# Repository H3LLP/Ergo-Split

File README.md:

# Ergo-Split
Ergonomic Split keyboard
A somewhat low-profile wireless 46-key keyboard that uses a dongle for connection.
Supports Choc V1 and V2 switches, is hotswappable, and uses a 3.7V 800mAh 802535 for each side. PCB is screwed into the case with 2 M2x6 screws and self-taps.

Dongle Case: https://www.printables.com/model/651428-seeed-xiao-ble-case-with-led-hole
(Not made by me)

Firmware is ZMK

AI Disclosure:
Used AI to help with part selection and parts of the firmware

The schematic for the PCB is the same for both sides

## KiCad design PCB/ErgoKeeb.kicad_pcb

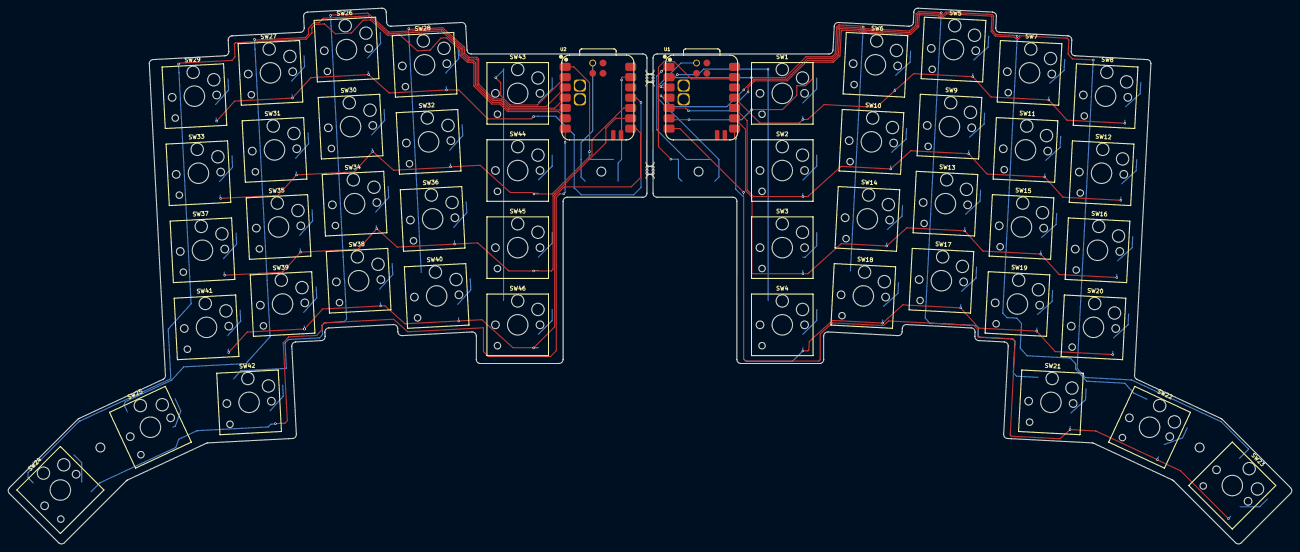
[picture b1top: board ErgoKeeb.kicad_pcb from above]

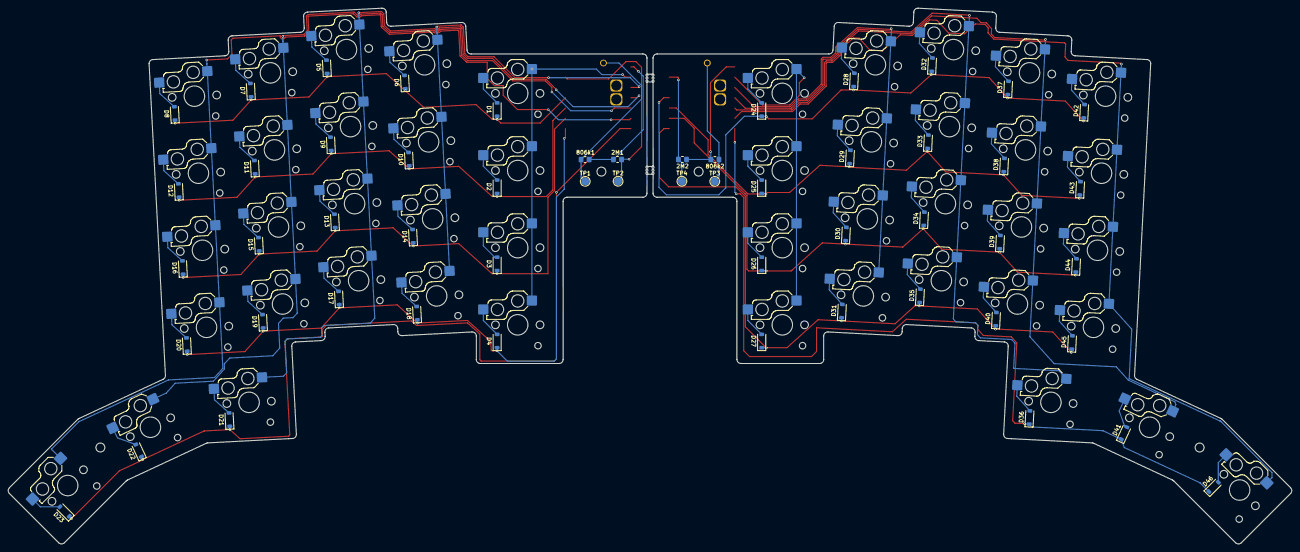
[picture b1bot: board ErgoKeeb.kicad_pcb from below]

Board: 2 copper layers, 316.9 x 132.3 mm, 108 parts (54 on the bottom side), 72 nets.

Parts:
2M1, 2M2: R3; R_0805_2012Metric_Pad1.20x1.40mm_HandSolder
806k1, 806k2: R1; R_0805_2012Metric_Pad1.20x1.40mm_HandSolder
BO1, BO2: MountingHole; mouse-bite-2mm-slot
D1, D2, D3, D4, D5, D6, D7, D8, D9, D10, D11, D12, D13, D14, D15, D16, D17, D18, D19, D20, D21, D22, D23, D24, D25, D26, D27, D28, D29, D30, D31, D32, D33, D34, D35, D36, D37, D38, D39, D40, D41, D42, D43, D44, D45, D46: D; D_SOD-123
H1, H2, H3, H4: MountingHole; MountingHole_2.2mm_M2
SW1, SW2, SW3, SW4, SW5, SW6, SW7, SW8, SW9, SW10, SW11, SW12, SW13, SW14, SW15, SW16, SW17, SW18, SW19, SW20, SW21, SW22, SW23, SW24, SW25, SW26, SW27, SW28, SW29, SW30, SW31, SW32, SW33, SW34, SW35, SW36, SW37, SW38, SW39, SW40, SW41, SW42, SW43, SW44, SW45, SW46: SW_Hotswap_Kailh_Choc_V1V2_1.00u
TP1, TP3: BAT; TestPoint_Pad_D2.0mm
TP2, TP4: GND; TestPoint_Pad_D2.0mm
U1, U2: XIAO-nRF52840-SMD; modified-XIAO-nRF52840-SMD

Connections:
/left/BT_PIN: 2M1.1, 806k1.2, U1.1 (D0)
/left/Ground: 2M1.2, TP2.1 (1_1), U1.13 (GND)
/left/VBAT: 806k1.1, TP1.1 (1_1), U1.19 (VBAT)
/left/col 0: SW1.1, SW2.1, SW3.1, SW4.1, U1.2 (D1)
/left/col 1: SW6.1, SW10.1, SW14.1, SW18.1, U1.3 (D2)
/left/col 2: SW5.1, SW9.1, SW13.1, SW17.1, SW21.1, U1.4 (D3)
/left/col 3: SW7.1, SW11.1, SW15.1, SW19.1, SW22.1, U1.5 (D4)
/left/col 4: SW8.1, SW12.1, SW16.1, SW20.1, SW23.1, U1.6 (D5)
/left/row 0: D1.1 (K), D5.1 (K), D6.1 (K), D7.1 (K), D8.1 (K), U1.11 (D10)
/left/row 1: D2.1 (K), D9.1 (K), D10.1 (K), D11.1 (K), D12.1 (K), U1.10 (D9)
/left/row 2: D3.1 (K), D13.1 (K), D14.1 (K), D15.1 (K), D16.1 (K), U1.9 (D8)
/left/row 3: D4.1 (K), D17.1 (K), D18.1 (K), D19.1 (K), D20.1 (K), U1.8 (D7)
/left/row 4: D21.1 (K), D22.1 (K), D23.1 (K), U1.7 (D6)
/right/BT_PIN: 2M2.1, 806k2.2, U2.1 (D0)
/right/Ground: 2M2.2, TP4.1 (1_1), U2.13 (GND)
/right/VBAT: 806k2.1, TP3.1 (1_1), U2.19 (VBAT)
/right/col 0: SW43.1, SW44.1, SW45.1, SW46.1, U2.2 (D1)
/right/col 1: SW28.1, SW32.1, SW36.1, SW40.1, U2.3 (D2)
/right/col 2: SW26.1, SW30.1, SW34.1, SW38.1, SW42.1, U2.4 (D3)
/right/col 3: SW25.1, SW27.1, SW31.1, SW35.1, SW39.1, U2.5 (D4)
/right/col 4: SW24.1, SW29.1, SW33.1, SW37.1, SW41.1, U2.6 (D5)
/right/row 0: D24.1 (K), D28.1 (K), D32.1 (K), D37.1 (K), D42.1 (K), U2.11 (D10)
/right/row 1: D25.1 (K), D29.1 (K), D33.1 (K), D38.1 (K), D43.1 (K), U2.10 (D9)
/right/row 2: D26.1 (K), D30.1 (K), D34.1 (K), D39.1 (K), D44.1 (K), U2.9 (D8)
/right/row 3: D27.1 (K), D31.1 (K), D35.1 (K), D40.1 (K), D45.1 (K), U2.8 (D7)
/right/row 4: D36.1 (K), D41.1 (K), D46.1 (K), U2.7 (D6)
unnamed: D1.2 (A), SW1.2
unnamed: D2.2 (A), SW2.2
unnamed: D3.2 (A), SW3.2
unnamed: D4.2 (A), SW4.2
unnamed: D5.2 (A), SW5.2
unnamed: D6.2 (A), SW6.2
unnamed: D7.2 (A), SW7.2
unnamed: D8.2 (A), SW8.2
unnamed: D9.2 (A), SW9.2
unnamed: D10.2 (A), SW10.2
unnamed: D11.2 (A), SW11.2
unnamed: D12.2 (A), SW12.2
unnamed: D13.2 (A), SW13.2
unnamed: D14.2 (A), SW14.2
unnamed: D15.2 (A), SW15.2
unnamed: D16.2 (A), SW16.2
unnamed: D17.2 (A), SW17.2
unnamed: D18.2 (A), SW18.2
unnamed: D19.2 (A), SW19.2
unnamed: D20.2 (A), SW20.2
unnamed: D21.2 (A), SW21.2
unnamed: D22.2 (A), SW22.2
unnamed: D23.2 (A), SW23.2
unnamed: D24.2 (A), SW43.2
unnamed: D25.2 (A), SW44.2
unnamed: D26.2 (A), SW45.2
unnamed: D27.2 (A), SW46.2
unnamed: D28.2 (A), SW28.2
unnamed: D29.2 (A), SW32.2
unnamed: D30.2 (A), SW36.2
unnamed: D31.2 (A), SW40.2
unnamed: D32.2 (A), SW26.2
unnamed: D33.2 (A), SW30.2
unnamed: D34.2 (A), SW34.2
unnamed: D35.2 (A), SW38.2
unnamed: D36.2 (A), SW42.2
unnamed: D37.2 (A), SW27.2
unnamed: D38.2 (A), SW31.2
unnamed: D39.2 (A), SW35.2
unnamed: D40.2 (A), SW39.2
unnamed: D41.2 (A), SW25.2
unnamed: D42.2 (A), SW29.2
unnamed: D43.2 (A), SW33.2
unnamed: D44.2 (A), SW37.2
unnamed: D45.2 (A), SW41.2
unnamed: D46.2 (A), SW24.2

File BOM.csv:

Part,Type,Quantity,Unit price (USD),Line total (USD),Link,Vendor,Funding,Notes,Designator,Footprint,Value
0805 SMD Resistor 2M Ohms,Part,2,2.81,2.81,https://www.aliexpress.us/item/3256806797741926.html,,Grant,,"2M1, 2M2",0805,R3
0805 SMD Resistor 806K Ohms,Part,2,2.27,2.27,https://www.aliexpress.us/item/3256804997915352.html,,Grant,,"806K1, 806K2",0805,R1
1N4148W T4 SOD-123,Part,46,3.60,3.60,https://www.aliexpress.us/item/3256811977042224.html,,Grant,,"D1, D10, D11, D12, D13, D14, D15, D16, D17, D18, D19, D2, D20, D21, D22, D23, D24, D25, D26, D27, D28, D29, D3, D30, D31, D32, D33, D34, D35, D36, D37, D38, D39, D4, D40, D41, D42, D43, D44, D45, D...",D_SOD-123,D
Kalih Choc Low Profile Socket,Part,46,7.37,7.37,https://www.aliexpress.us/item/3256808357010978.html,,Grant,,"SW1, SW10, SW11, SW12, SW13, SW14, SW15, SW16, SW17, SW18, SW19, SW2, SW20, SW21, SW22, SW23, SW24, SW25, SW26, SW27, SW28, SW29, SW3, SW30, SW31, SW32, SW33, SW34, SW35, SW36, SW37, SW38, SW39, SW...",SW_Hotswap_Kailh_Choc_V1V2_1.00u,~
XIAO nRF52840,Part,3,32.08,32.08,https://www.aliexpress.us/item/3256808047100037.html,,Grant,,"U1, U2",modified-XIAO-nRF52840-SMD,XIAO-nRF52840-SMD
Any Choc V1/V2 Switches,Part,46,28.23,28.23,https://www.aliexpress.us/item/3256808697103313.html,,Grant,,~,~,~
3.7V 800mAh 802535,Part,2,5.99,5.99,https://www.aliexpress.us/item/3256804695633953.html,,Grant,,~,~,~
Left Case + Right Case,3D printed,2,17.06,17.06,,,Paying myself,JLC3DP,~,~,~
keycaps,Part,46,15.04,14.72,,,Grant,JLC3DP,~,~,~
PCB,PCB,1,24.20,24.20,,,Grant,JLCPCB,~,~,~
M2*6 Screws,Part,4,1.55,1.55,https://www.aliexpress.us/item/2251832624557792.html,,Already own,,~,~,~
Shipping,Shipping,1,,40.65,,,Grant,,,,
Total,,,,180.53,,,,,,,
Grant total,,,,161.92,,,,,,,
